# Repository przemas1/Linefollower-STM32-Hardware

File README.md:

# Linefollower-STM32-Hardware
These are some simple Linefollower schematics I did a while ago. It was my first MCU hardware project so I know there is a lot of room for improvement.
It uses 6 CNY70 photocouplers, and two DC motors. For motor control I used L289N and for MCU I chose an STM32F101.

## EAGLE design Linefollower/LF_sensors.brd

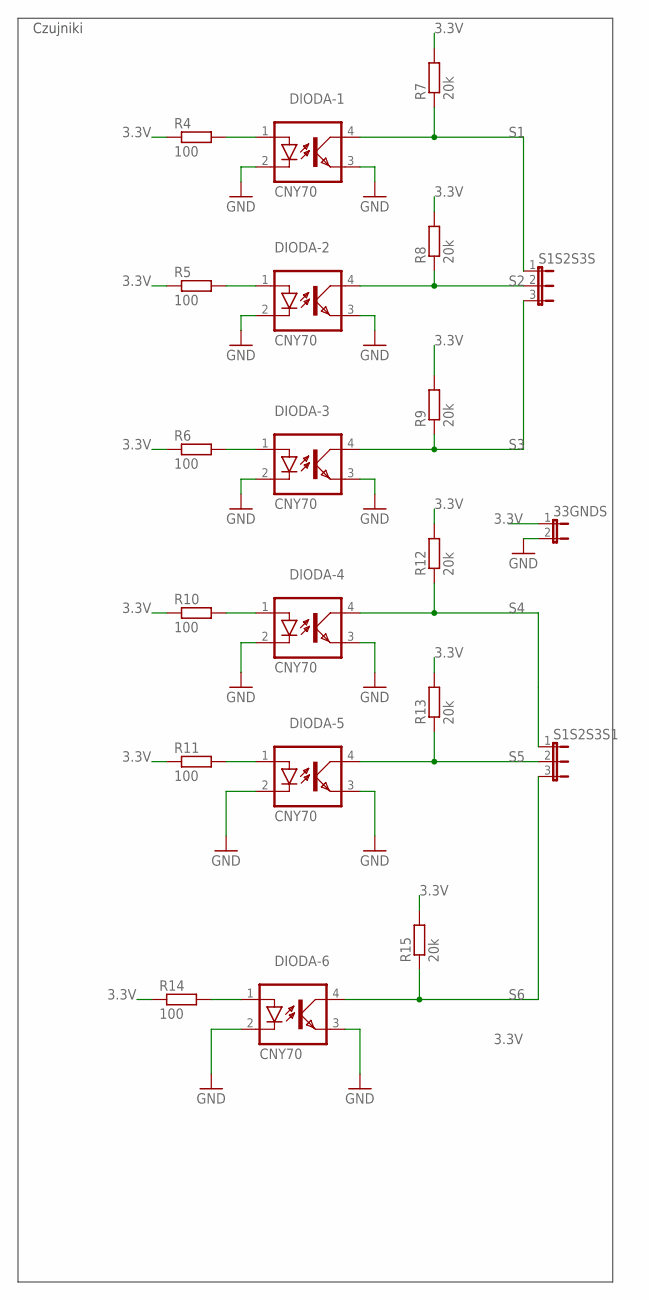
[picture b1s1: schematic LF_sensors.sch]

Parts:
33GNDS: JP1E; JP1
DIODA-1, DIODA-2, DIODA-3, DIODA-4, DIODA-5, DIODA-6: CNY70; DIL04
R4, R5, R6, R10, R11, R14: 100; R0805
R7, R8, R9, R12, R13, R15: 20k; R0805
S1S2S3S, S1S2S3S1: JP2E; JP2

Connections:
3.3V: 33GNDS.1, R4.1, R5.1, R6.1, R7.2, R8.2, R9.2, R10.1, R11.1, R12.2, R13.2, R14.1, R15.2
GND: 33GNDS.2, DIODA-1.2 (C), DIODA-1.3 (EMIT), DIODA-2.2 (C), DIODA-2.3 (EMIT), DIODA-3.2 (C), DIODA-3.3 (EMIT), DIODA-4.2 (C), DIODA-4.3 (EMIT), DIODA-5.2 (C), DIODA-5.3 (EMIT), DIODA-6.2 (C), DIODA-6.3 (EMIT)
unnamed: DIODA-6.1 (A), R14.2
unnamed: DIODA-1.1 (A), R4.2
unnamed: DIODA-2.1 (A), R5.2
unnamed: DIODA-3.1 (A), R6.2
unnamed: DIODA-4.1 (A), R10.2
unnamed: DIODA-5.1 (A), R11.2
S1: DIODA-1.4 (COL), R7.1, S1S2S3S.1
S2: DIODA-2.4 (COL), R8.1, S1S2S3S.2
S3: DIODA-3.4 (COL), R9.1, S1S2S3S.3
S4: DIODA-4.4 (COL), R12.1, S1S2S3S1.1
S5: DIODA-5.4 (COL), R13.1, S1S2S3S1.2
S6: DIODA-6.4 (COL), R15.1, S1S2S3S1.3

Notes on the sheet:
Czujniki

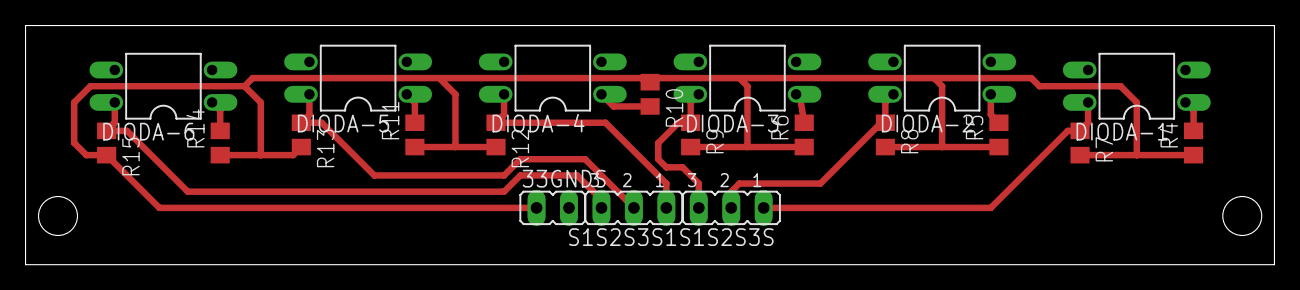
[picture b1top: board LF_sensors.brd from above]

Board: 2 copper layers, 97.8 x 18.7 mm, 21 parts (0 on the bottom side), 14 nets.

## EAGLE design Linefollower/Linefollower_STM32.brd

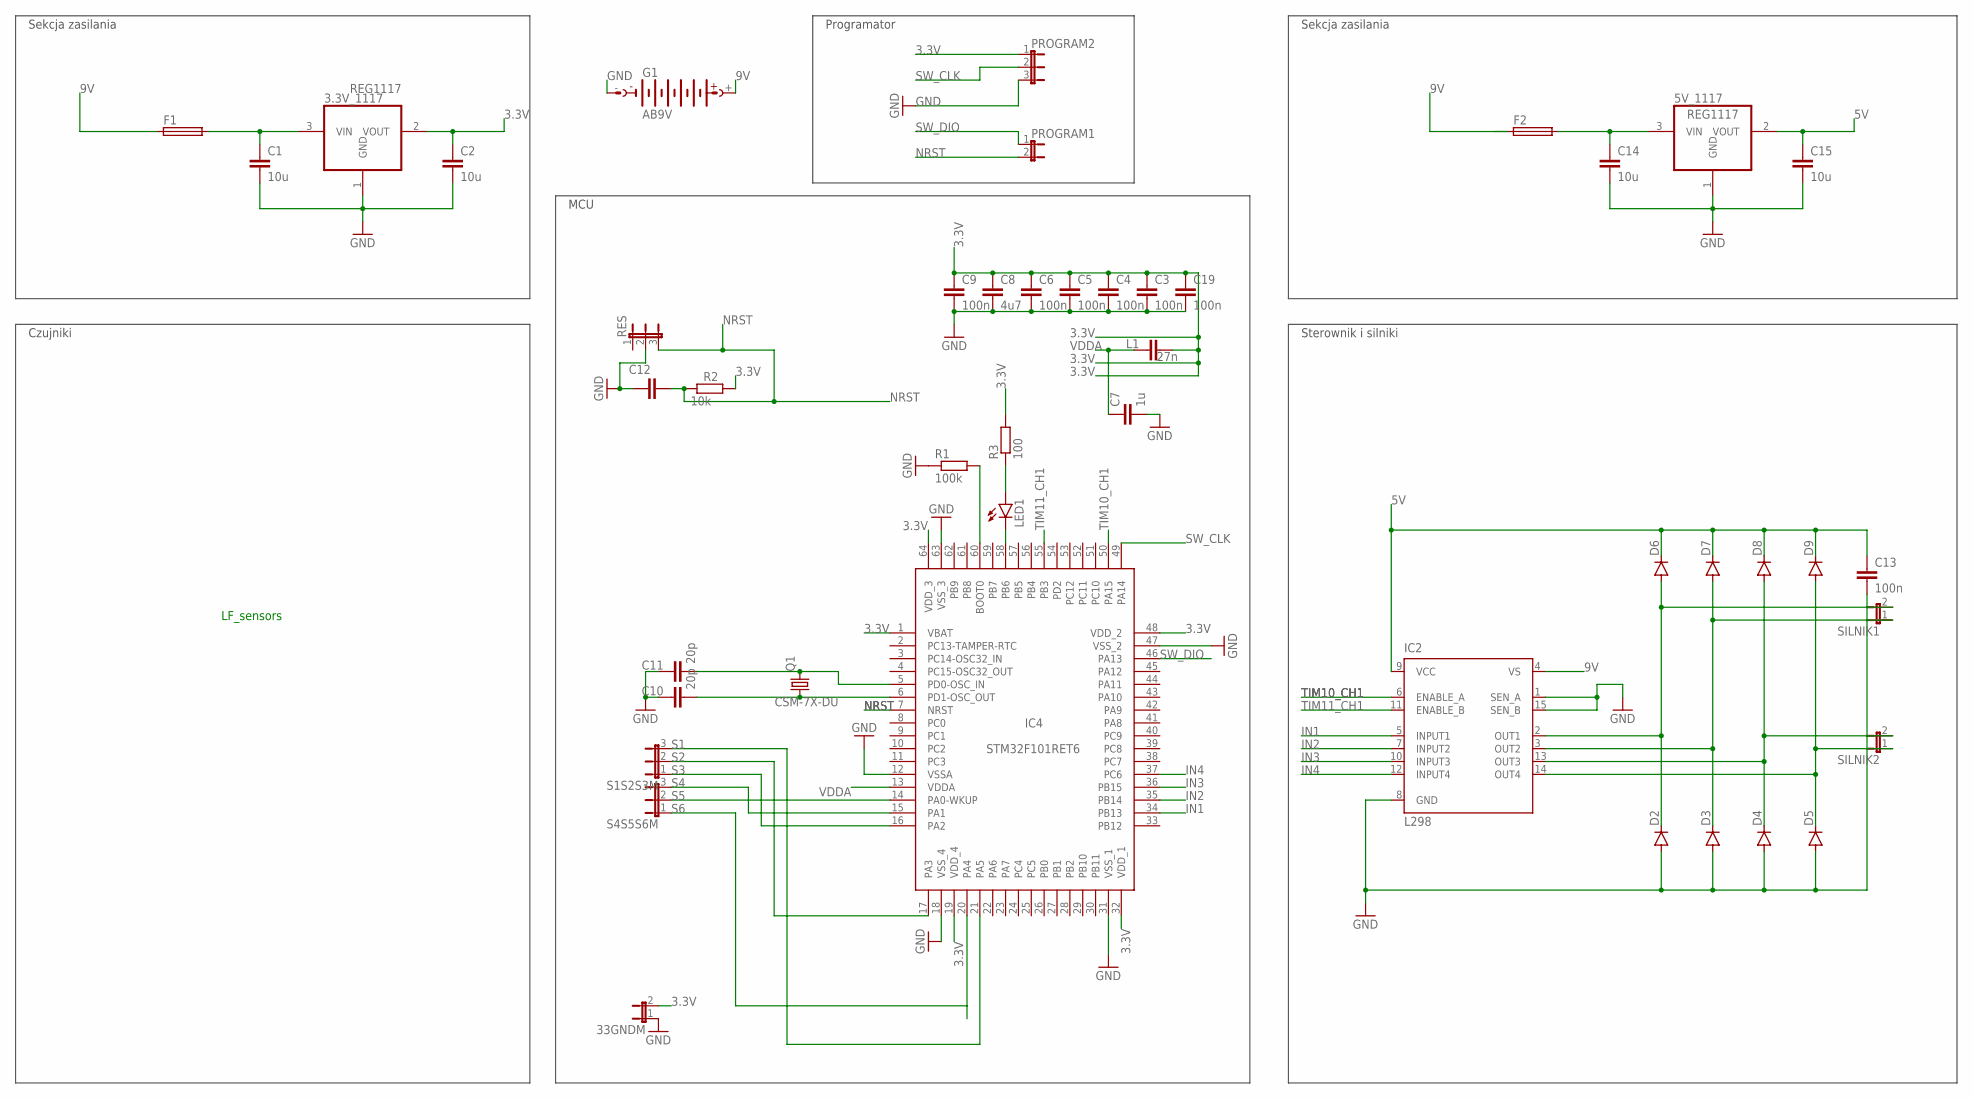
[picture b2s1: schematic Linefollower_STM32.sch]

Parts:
3.3V_1117, 5V_1117: REG1117; SOT223
33GNDM: JP1E; JP1
C1, C2, C14, C15: 10u; C0805
C3, C4, C5, C6, C9, C13, C19: 100n; C0805
C7: 1u; C0805
C8: 4u7; C0805
C10, C11: 20p; C0805
C12: C-EUC0805; C0805
D2, D3, D4, D5, D6, D7, D8, D9: DIODE-DO214AA; DO214AA
F1, F2: TE5
G1: AB9V
IC2: L298; MULTIWATT-15
IC4: STM32F101RET6; QFP50P1200X1200X160-64N
L1: 27n; C0805
LED1: LEDSML1206; SML1206
PROGRAM1: JP1E; JP1
PROGRAM2: JP2E; JP2
Q1: CSM-7X-DU
R1: 100k; R0805
R2: 10k; R0805
R3: 100; R0805
RES: JP2E; JP2
S1S2S3M, S4S5S6M: JP2E; JP2
SILNIK1, SILNIK2: JP1E; JP1

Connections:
3.3V: 3.3V_1117.2 (VOUT), 33GNDM.2, C2.1, C3.1, C4.1, C5.1, C6.1, C8.1, C9.1, C19.1, IC4.1 (VBAT), IC4.19 (VDD_4), IC4.32 (VDD_1), IC4.48 (VDD_2), IC4.64 (VDD_3), L1.2, PROGRAM2.1, R2.2, R3.2
5V: 5V_1117.2 (VOUT), C13.1, C15.1, D6.C, D7.C, D8.C, D9.C, IC2.9 (VCC)
9V: F1.1, F2.1, G1.+, IC2.4 (VS)
GND: 3.3V_1117.1 (GND), 5V_1117.1 (GND), 33GNDM.1, C1.2, C2.2, C3.2, C4.2, C5.2, C6.2, C7.2, C8.2, C9.2, C10.1, C11.1, C12.1, C13.2, C14.2, C15.2, C19.2, D2.A, D3.A, D4.A, D5.A, G1.-, IC2.1 (SEN_A), IC2.8 (GND), IC2.15 (SEN_B), IC4.12 (VSSA), IC4.18 (VSS_4), IC4.31 (VSS_1), IC4.47 (VSS_2), IC4.63 (VSS_3), PROGRAM2.3, R1.1, RES.2
IN1: IC2.5 (INPUT1), IC4.34 (PB13)
IN2: IC2.7 (INPUT2), IC4.35 (PB14)
IN3: IC2.10 (INPUT3), IC4.36 (PB15)
IN4: IC2.12 (INPUT4), IC4.37 (PC6)
unnamed: C10.2, IC4.6 (PD1-OSC_OUT), Q1.1
unnamed: C7.1, IC4.13 (VDDA), L1.1
unnamed: 3.3V_1117.3 (VIN), C1.1, F1.2
unnamed: C11.2, IC4.5 (PD0-OSC_IN), Q1.2
unnamed: IC4.60 (BOOT0), R1.2
unnamed: IC4.58 (PB6), LED1.C
unnamed: LED1.A, R3.1
unnamed: D2.C, D6.A, IC2.2 (OUT1), SILNIK1.2
unnamed: D3.C, D7.A, IC2.3 (OUT2), SILNIK1.1
unnamed: D4.C, D8.A, IC2.13 (OUT3), SILNIK2.2
unnamed: D5.C, D9.A, IC2.14 (OUT4), SILNIK2.1
unnamed: 5V_1117.3 (VIN), C14.1, F2.2
NRST: C12.2, IC4.7 (NRST), PROGRAM1.2, R2.1, RES.3
unnamed: IC4.20 (PA4), S4S5S6M.1
S2: IC4.17 (PA3), S1S2S3M.2
S3: IC4.16 (PA2), S1S2S3M.1
S4: IC4.15 (PA1), S4S5S6M.3; also elsewhere on the board
S$7: IC4.21 (PA5), S1S2S3M.3
S$11: IC4.14 (PA0-WKUP), S4S5S6M.2; also elsewhere on the board
SW_CLK: IC4.49 (PA14), PROGRAM2.2
SW_DIO: IC4.46 (PA13), PROGRAM1.1
TIM10_CH1: IC2.6 (ENABLE_A), IC4.50 (PA15)
TIM11_CH1: IC2.11 (ENABLE_B), IC4.55 (PB3)

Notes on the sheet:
Sekcja zasilania
Programator
MCU
Czujniki
Sterownik i silniki
LF_sensors

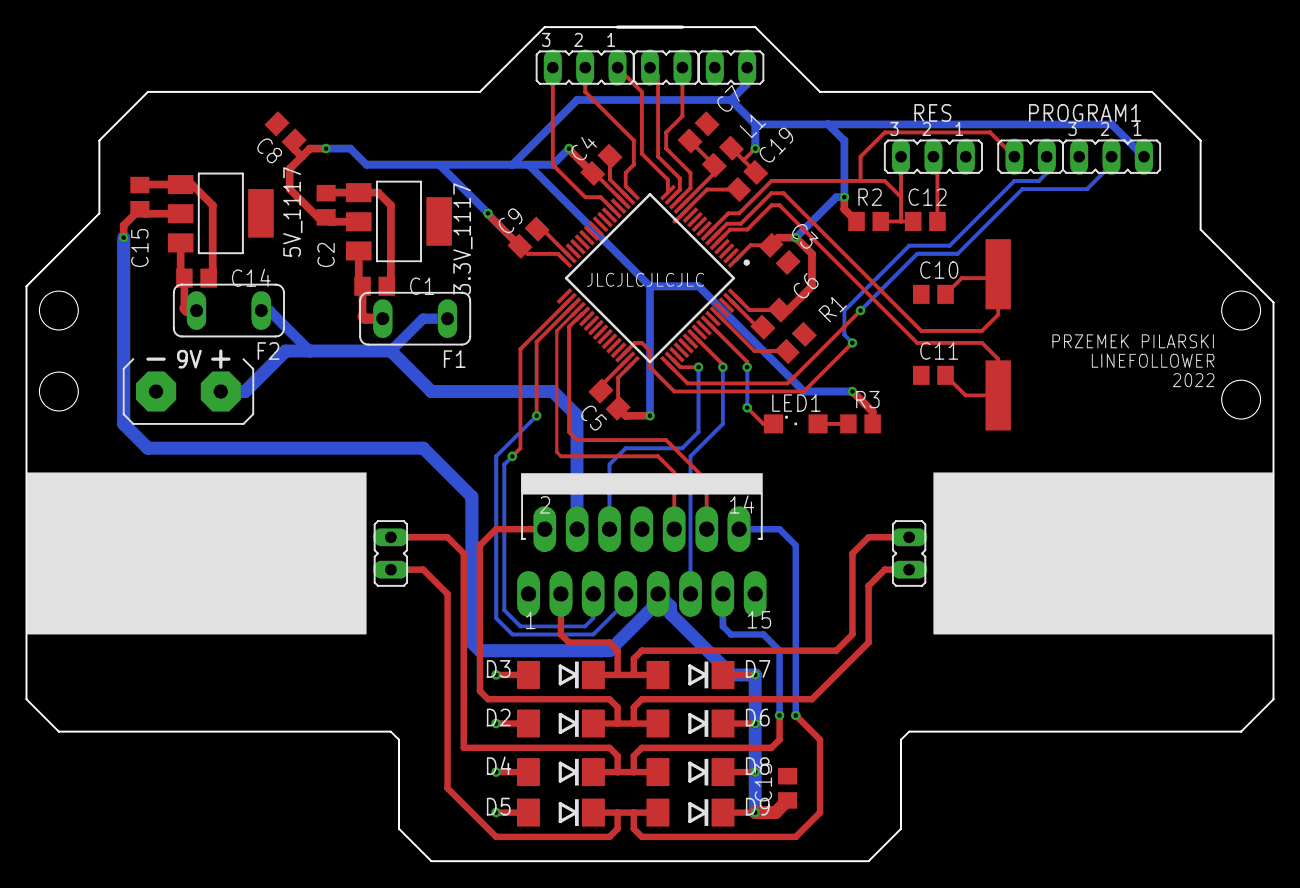
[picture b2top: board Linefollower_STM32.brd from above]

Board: 2 copper layers, 97.8 x 65.4 mm, 45 parts (0 on the bottom side), 30 nets.

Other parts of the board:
S4S5M: JP1

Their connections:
S4: S4S5M.2; also elsewhere on the board
S$11: S4S5M.1; also elsewhere on the board

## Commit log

2022-07-05 6 sensor strip
